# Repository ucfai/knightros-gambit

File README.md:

# Knightr0's Gambit

## Overview
This repository hosts the code for Knightr0's Gambit, a [University of Central Florida](https://www.ucf.edu) [AI](https://ucfai.org) / [IEEE](https://ieee.cecs.ucf.edu) collaboration to create an automatic chessboard (similar to [Harry Potter's Wizard Chess](https://www.youtube.com/watch?v=s3cjWc-XXCg) with less violence) powered by a custom chess AI.

<!--  -->

<!-- Video of chessboard in action: https://youtu.be/blah -->

[Project webpage](https://ucfai.github.io/knightros-gambit/), [project overview doc](https://docs.google.com/document/d/1CPY9yEVWDVO99mbckBnCJi-gKKobkBnB4XnjrLc4HFs/edit#)

<!-- Build guide: n/a -->

## How it works
<!--  -->
The main program is `game.py` (located in `firmware/raspi/`). This code is the entry point to interacting with the chessboard; it runs a loop that keeps track of game state (whose turn it is, past moves, etc.), computes moves using a custom chess AI, and processes images taken of the board to compute board state after the player moves a piece. This driver program has options for over-the-board play, a command-line interface, and a web interface. We plan to add a voice interface at a later point.

The `game.py` program runs on a Raspberry Pi, and interacts with arduino code that controls the actuators of the chessboard, the four interfaces (one-at-a-time) described above, a custom AI modeled after Deepmind's AlphaZero, and a computer vision system which keeps track of the current chessboard state.

The arduino code (located in `firmware/arduino/chessboard`) runs on an ESP32 microcontroller. 
Once the AI move has been computed on the Raspberry Pi, it is converted to a standardized message format and sent to the ESP32 microcontroller using UART serial communication. The microcontroller then actuates the physical board mechanism (motors and electromagnet) and sends back status messages indicating current state of the board/microcontroller. UART serial communication is used as it allows us to easily send data in both directions.

The AI is modeled after [Deepmind's AlphaZero](https://deepmind.com/blog/article/alphazero-shedding-new-light-grand-games-chess-shogi-and-go).
> To learn each game, an untrained neural network plays millions of games against itself via a process of trial and error called reinforcement learning. At first, it plays completely randomly, but over time the system learns from wins, losses, and draws to adjust the parameters of the neural network, making it more likely to choose advantageous moves in the future.

> The trained network is used to guide a search algorithm – known as Monte-Carlo Tree Search (MCTS) – to select the most promising moves in games. For each move, AlphaZero searches only a small fraction of the positions considered by traditional chess engines. In Chess, for example, it searches only 60 thousand positions per second in chess, compared to roughly 60 million for Stockfish.

<!-- A system diagram of the Arduino is shown below. -->
<!--  -->

<!-- ## How to Build Chessboard
Main documentation: blah.com

You can find the bill of materials, assembly instructions, software setup, etc at this website.
 -->

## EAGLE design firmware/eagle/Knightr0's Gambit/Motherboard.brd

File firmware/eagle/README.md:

# EAGLE Files
This directory will hold all of the files needed to open and view the EAGLE PCB design.

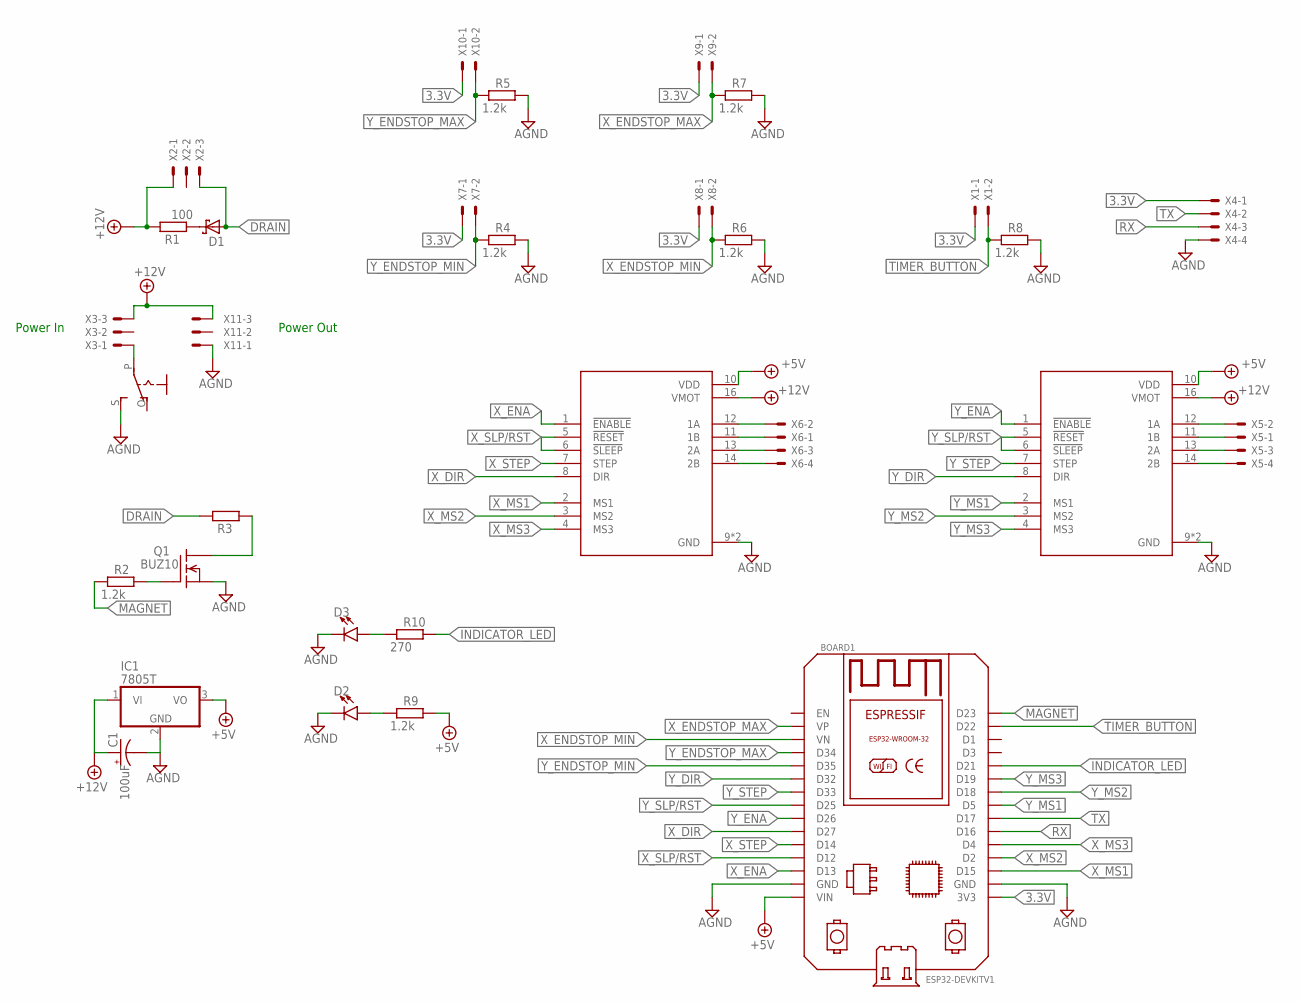
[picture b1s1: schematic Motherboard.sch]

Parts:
BOARD1: ESP32DEVKITV1; ESP32-DEVKITV1
C1: 100uF; B45181A
D1: SCHOTTKY-DIODEDO41; DO41-10
D2, D3: LED0603; LED-0603
IC1: 7805T; TO220H
Q1: BUZ10; TO220
R1: 100; R0603
R2, R4, R5, R6, R7, R8, R9: 1.2k; R0603
R3: R-EU_R0603; R0603
R10: 270; R0603
S1: EG1218S; EG1218
U1, U2: A4988_STEPPER_MOTOR_DRIVER_CARRIER; MODULE_A4988_STEPPER_MOTOR_DRIVER_CARRIER
X1, X7, X8, X9, X10: 22-23-2021
X2, X3, X11: 22-23-2031
X4, X5, X6: 22-23-2041

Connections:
3.3V: BOARD1.3V3, X1.1, X4.1, X7.1, X8.1, X9.1, X10.1
+5V: BOARD1.VIN, IC1.3 (VO), R9.2, U1.10 (VDD), U2.10 (VDD)
+12V: C1.+, IC1.1 (VI), R1.2, U1.16 (VMOT), U2.16 (VMOT), X2.1, X3.3, X11.3
AGND: BOARD1.GND, BOARD1.GND@1 (GND), C1.-, D2.C, D3.C, IC1.2 (GND), Q1.3 (S), R4.2, R5.2, R6.2, R7.2, R8.2, S1.S, U1.9 (GND), U1.15 (GND), U2.9 (GND), U2.15 (GND), X4.4, X11.1
DRAIN: D1.A, R3.2, X2.3
INDICATOR_LED: BOARD1.D21, R10.2
MAGNET: BOARD1.D23, R2.1
unnamed: U2.12 (1A), X5.2
unnamed: U2.11 (1B), X5.1
unnamed: U2.13 (2A), X5.3
unnamed: U2.14 (2B), X5.4
unnamed: U1.12 (1A), X6.2
unnamed: U1.11 (1B), X6.1
unnamed: D2.A, R9.1
unnamed: D3.A, R10.1
unnamed: Q1.2 (D), R3.1
unnamed: Q1.1 (G), R2.2
unnamed: D1.C, R1.1
unnamed: S1.P, X3.1
unnamed: U1.13 (2A), X6.3
unnamed: U1.14 (2B), X6.4
RX: BOARD1.D16, X4.3
TIMER_BUTTON: BOARD1.D22, R8.1, X1.2
TX: BOARD1.D17, X4.2
X_DIR: BOARD1.D27, U1.8 (DIR)
X_ENA: BOARD1.D13, U1.1 (!ENABLE)
X_ENDSTOP_MAX: BOARD1.VP, R7.1, X9.2
X_ENDSTOP_MIN: BOARD1.VN, R6.1, X8.2
X_MS1: BOARD1.D15, U1.2 (MS1)
X_MS2: BOARD1.D2, U1.3 (MS2)
X_MS3: BOARD1.D4, U1.4 (MS3)
X_SLP/RST: BOARD1.D12, U1.5 (!RESET), U1.6 (!SLEEP)
X_STEP: BOARD1.D14, U1.7 (STEP)
Y_DIR: BOARD1.D32, U2.8 (DIR)
Y_ENA: BOARD1.D26, U2.1 (!ENABLE)
Y_ENDSTOP_MAX: BOARD1.D34, R5.1, X10.2
Y_ENDSTOP_MIN: BOARD1.D35, R4.1, X7.2
Y_MS1: BOARD1.D5, U2.2 (MS1)
Y_MS2: BOARD1.D18, U2.3 (MS2)
Y_MS3: BOARD1.D19, U2.4 (MS3)
Y_SLP/RST: BOARD1.D25, U2.5 (!RESET), U2.6 (!SLEEP)
Y_STEP: BOARD1.D33, U2.7 (STEP)

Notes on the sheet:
Power In
Power Out

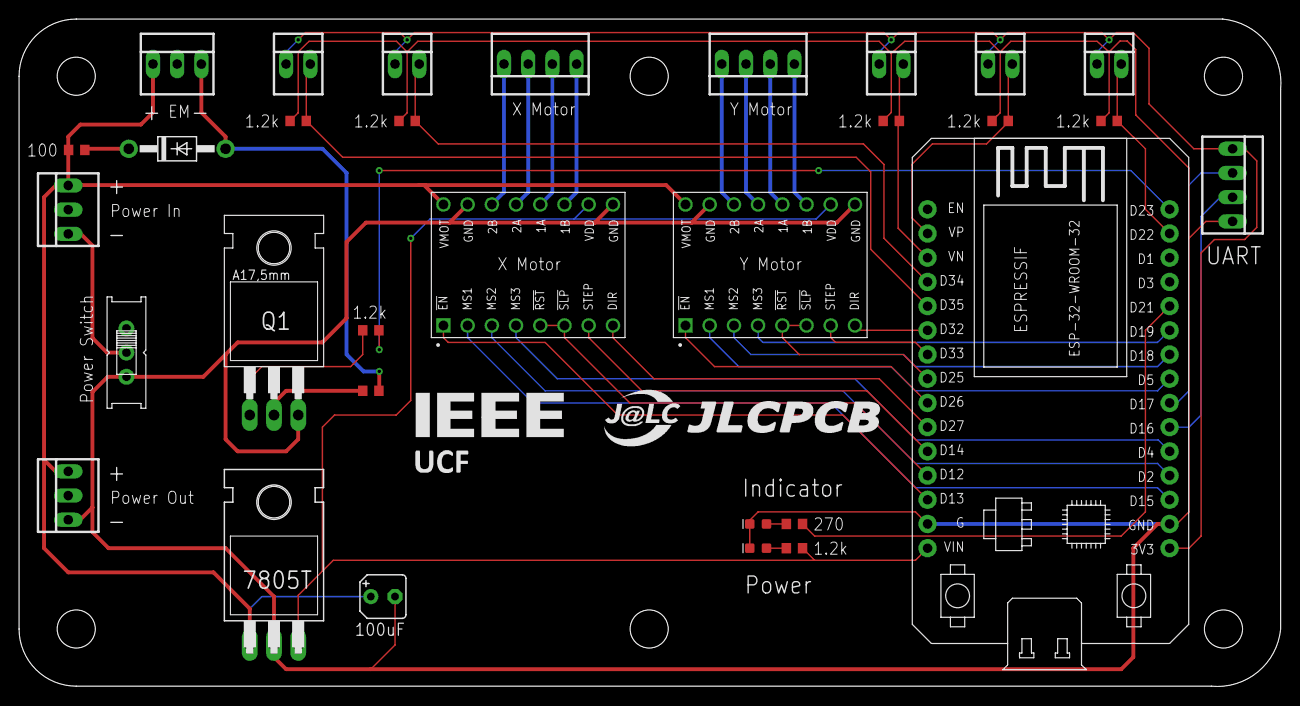
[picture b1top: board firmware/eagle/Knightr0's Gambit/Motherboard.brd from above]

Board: 2 copper layers, 132.4 x 70.0 mm, 31 parts (0 on the bottom side), 42 nets.

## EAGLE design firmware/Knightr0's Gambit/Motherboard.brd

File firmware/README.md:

# Firmware
This directory will hold code that controls actuation/sensing of the physical chessboard, as well as communication between the Arduino and the Raspberry Pi

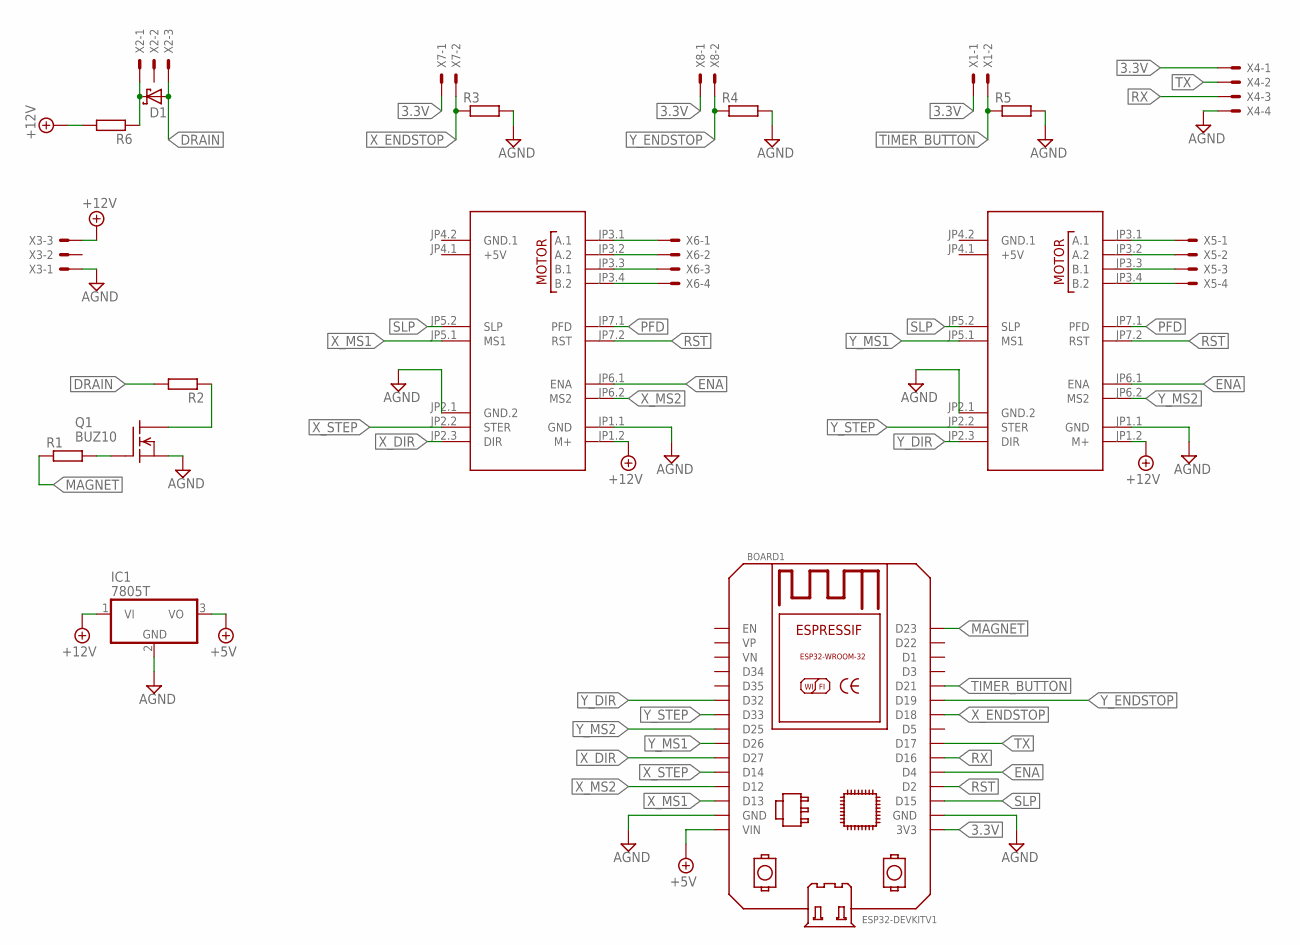
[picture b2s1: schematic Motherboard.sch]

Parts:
BOARD1: ESP32DEVKITV1; ESP32-DEVKITV1
D1: SCHOTTKY-DIODECB417-15; CB417-15
IC1: 7805T; TO220H
Q1: BUZ10; TO220
R1, R2, R3, R4, R5, R6: R-EU_R0603; R0603
U$1, U$2: STEPPER-MOTOR-EASY-DRIVER
X1, X7, X8: 22-23-2021
X2, X3: 22-23-2031
X4, X5, X6: 22-23-2041

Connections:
3.3V: BOARD1.3V3, X1.1, X4.1, X7.1, X8.1
+5V: BOARD1.VIN, IC1.3 (VO)
+12V: IC1.1 (VI), R6.2, U$1.JP1.2 (M+), U$2.JP1.2 (M+), X3.3
AGND: BOARD1.GND, BOARD1.GND@1 (GND), IC1.2 (GND), Q1.3 (S), R3.2, R4.2, R5.2, U$1.JP1.1 (GND), U$1.JP2.1 (GND.2), U$2.JP1.1 (GND), U$2.JP2.1 (GND.2), X3.1, X4.4
DRAIN: D1.A, R2.2, X2.3
ENA: BOARD1.D4, U$1.JP6.1 (ENA), U$2.JP6.1 (ENA)
MAGNET: BOARD1.D23, R1.1
unnamed: U$1.JP3.1 (A.1), X6.1
unnamed: U$1.JP3.2 (A.2), X6.2
unnamed: U$1.JP3.3 (B.1), X6.3
unnamed: U$1.JP3.4 (B.2), X6.4
unnamed: U$2.JP3.1 (A.1), X5.1
unnamed: U$2.JP3.2 (A.2), X5.2
unnamed: U$2.JP3.3 (B.1), X5.3
unnamed: U$2.JP3.4 (B.2), X5.4
unnamed: Q1.2 (D), R2.1
unnamed: Q1.1 (G), R1.2
unnamed: D1.C, R6.1, X2.1
PFD: U$1.JP7.1 (PFD), U$2.JP7.1 (PFD)
RST: BOARD1.D2, U$1.JP7.2 (RST), U$2.JP7.2 (RST)
RX: BOARD1.D16, X4.3
SLP: BOARD1.D15, U$1.JP5.2 (SLP), U$2.JP5.2 (SLP)
TIMER_BUTTON: BOARD1.D21, R5.1, X1.2
TX: BOARD1.D17, X4.2
X_DIR: BOARD1.D27, U$1.JP2.3 (DIR)
X_ENDSTOP: BOARD1.D18, R3.1, X7.2
X_MS1: BOARD1.D13, U$1.JP5.1 (MS1)
X_MS2: BOARD1.D12, U$1.JP6.2 (MS2)
X_STEP: BOARD1.D14, U$1.JP2.2 (STER)
Y_DIR: BOARD1.D32, U$2.JP2.3 (DIR)
Y_ENDSTOP: BOARD1.D19, R4.1, X8.2
Y_MS1: BOARD1.D26, U$2.JP5.1 (MS1)
Y_MS2: BOARD1.D25, U$2.JP6.2 (MS2)
Y_STEP: BOARD1.D33, U$2.JP2.2 (STER)

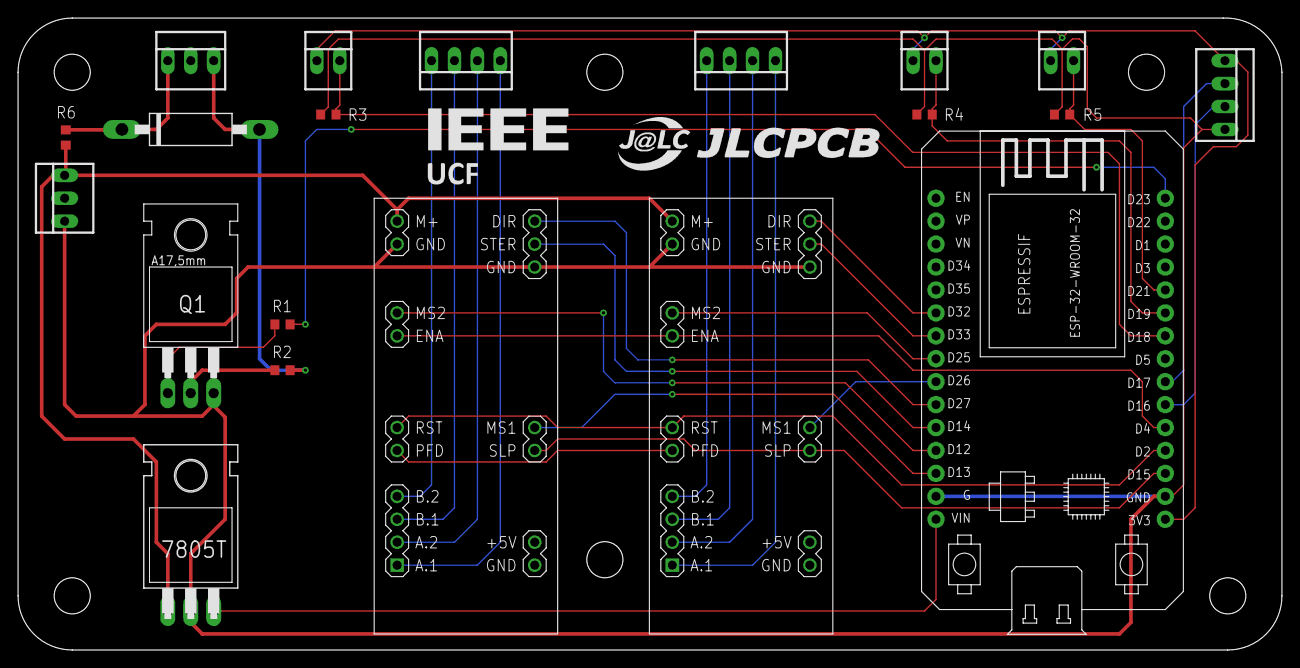
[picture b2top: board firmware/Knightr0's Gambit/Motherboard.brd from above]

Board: 2 copper layers, 140.0 x 70.0 mm, 20 parts (0 on the bottom side), 34 nets.

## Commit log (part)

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2022-02-13 changed homeAxis to allow for alignment of positive extremes as well
2022-02-13 Create stockfish wrapper to allow system agnostic creation of Stockfish object in stockfish_train
2022-02-13 Add ALIGN_AXIS and SET_ELECTROMAGNET opcodes
2022-02-13 Add clarifying comment to Message docstring
2022-02-13 Add function to request retransmitting last msg
2022-02-14 io file update
2022-02-15 Moved message processing and transmit function calls
2022-02-15 added spacing in alignAxis for readability
2022-02-15 fixed order of enum
2022-02-15 Removed .vscode folder and added .vscode directory name to .gitignore
2022-02-16 Add parser based on Lucas's prototype code
2022-02-16 modified motor direction preprocessors for clarification
2022-02-17 removed return in load_model
2022-02-17 Fixed device bug
2022-02-17 Resolved PR comments
2022-02-17 Created streamlit branch and added dashboard file
2022-02-17 Add README description explaining how to invoke train.py
2022-02-17 Fix import order in train
2022-02-17 Add dummy requirements.txt
2022-02-17 add newline
2022-02-19 Updated train.py to work with the dashboard and added additional features to the dashboard
2022-02-19 added comments for previous changes and fixed alignAxis current position computation placement
2022-02-22 Update argument handling to remove globals
2022-02-22 Remove test files from PR
2022-02-22 Print every 10th game
2022-02-24 Update streamlit dashboard
2022-02-24 Add debug messages to train.py
2022-02-24 Revert "Add arg parser to game"
2022-02-24 Fix outdated debug message in train.sh
    When arg is not streamlit or json, train.sh currently prints
    "Expected first argument to be either <streamlit> or <cli>" which is incorrect.
2022-02-24 Fixed 0/0 bug
2022-02-24 typo : )
2022-02-24 Made training flags, split stock dataset creation Also made it so it doesnt crash if the dataset directory doesnt exist
2022-02-25 Added new end stop switches
2022-02-25 Changed the name of errorFlag to uartMessageIncompleteFlag for clarity
2022-02-26 Changed to new pinout for endstops
2022-02-27 added necessary PWM setup for future ledcWrite use
2022-02-27 fixed further style mistakes
2022-03-01 Move arg parsing to util
2022-03-01 Calling .reverse() on chess_grid lead to bug with piece captures. Fixed
2022-03-01 Add parsing of pgn file to list of uci_moves
2022-03-01 Fix docstring
2022-03-01 Update parse_test_file
2022-03-01 Update comments in parse_test_file
2022-03-01 Move game loop into class based approach with process method
2022-03-01 Add methods to expose info needed for GUI
2022-03-01 Fix scholar's mate
2022-03-01 Added definitions for OpCode and ArduinoStatus message lengths
2022-03-02 Update test1.txt to have same commands as test1.pgn, but expressed as Message types
2022-03-02 Add test file with Instruction type messages
2022-03-02 Add function for transposing a board cell
2022-03-02 Fix pylint errors
2022-03-03 updated member page
2022-03-08 corrected error handling function format and removed incorrect function calls
2022-03-09 corrected comment
2022-03-12 update eagle files
2022-03-13 Update align axis to allow more granularity. Can now specify to align with xmin, xmax, ymin, or ymax.
2022-03-13 Remove text from buttons
2022-03-13 Remove dead lines
2022-03-15 implemented main structure of movement functions
2022-03-15 updated point calculations and accounted for potential edge cases
2022-03-16 Changed order of values in message array for sendMessageToPi()
2022-03-16 Fixed indexing for Instruction messages
2022-03-17 added msd and updated links
2022-03-18 Added comment to explain sentMessage[]
2022-03-19 removed old implementation of movement primitive calls
2022-03-19 added remaining cases for moveAlongEdges
2022-03-19 added movement function result handling and updated format
2022-03-22 Added comments
2022-03-22 Updated return value
2022-03-23 Updated recursive call, naming, and comments
2022-03-23 Updated recursive call and added comments explaining it
2022-03-23 Added edge case where moveDirect is used to path to starting point with an invalid slope
2022-03-24 Simplified repeated code using a pointer for the motor
2022-03-24 Updated statusCodeHandler behavior and related calls
2022-03-24 Simplified code with updated handler logic, fixed incorrect return
2022-03-24 Updated residual layers
2022-03-25 Updated moveDirect so electromagnet accounts for moving to the start position
2022-03-25 Added comment
2022-03-25 Fixed path issue
2022-03-26 Fix order of return statement
2022-03-26 Update shebang line in bash script so that it works for zsh shell
2022-03-26 Add TrainingFlags class to simplify return statements and fixed pylint errors
2022-03-26 Fix variable naming
2022-03-29 Add structure for page frames and fix coloring of cells
2022-03-29 Update Instruction message handling scheme and add calls to alignaxis
2022-03-29 Update InstructionType enum, fixed message validation
2022-03-30 Make directory for opcodegenerator
2022-03-30 implement frames for each page, added page for centering piece
2022-03-30 Fix some pylint warnings
2022-03-31 started alignAxis adjustment for further review
2022-03-31 Corrected code in accordance to functionality and added comments
2022-03-31 Fixed valid range for ALIGN_AXIS extra byte
2022-03-31 Testing API Key as environment variable
2022-03-31 comment change
2022-03-31 Getting figshare api set up
2022-04-01 Added debug flag
2022-04-01 Added debug messages to main functions
2022-04-01 Updated debug print statements and comments
2022-04-01 Updated tab width to 2 spaces
2022-04-01 Updated spacing for while loops
2022-04-01 Updated spacing surrounding && and || comparisons to one space
2022-04-01 Updated name and comments
2022-04-02 Updated equal and not equal comparisons
2022-04-02 Wrapped repeated code into a function
2022-04-02 Updated for loops to remove variable declaration inside the loop argument fields
2022-04-02 Updated spacing
2022-04-02 Add code for calling home() on Arduino directly. Also changed OpType to InstructionType
2022-04-02 Updated preprocessors to enums for better organization
2022-04-02 Updated enum index name
2022-04-03 Update message sending to send bytes
2022-04-03 Implement receiving messages from Arduino, safeguard all comms with --microcontroller flag
2022-04-03 Update if statement to use is None comparison
2022-04-03 Fix serial import order and function call to check if buffer is nonempty
2022-04-03 Updated variable and function argument datatypes to reduce wasted memory
2022-04-03 Fixed compilation errors
2022-04-03 Getting the figshare API to work with current ways of saving dataset and models
2022-04-03 Updated variable names to be consistent with similar variables in movementFunction.ino
2022-04-04 Remove out-of-date TODOs and make other small fixes
2022-04-04 Update all docstrings to use triple quotes
2022-04-04 Add disable import error for 3P libraries
2022-04-04 Removed unnecessary newline spaces
2022-04-04 Removed curly braces from if statement with single line of code
2022-04-04 Fixed alignAxis bug and formatting
2022-04-04 Removed eighthStepsPerPulse since it was not used, also updated formatting accordingly
2022-04-04 Short term fix to replace SerialEvent2()
2022-04-05 Added buffer clear on duplicates
2022-04-05 Initial model evaluation code
2022-04-05 Updated debug print statements to use debug levels instead
2022-04-05 Removed testing.py
2022-04-06 Update prompt when running in debug mode
2022-04-07 Added semi-colon to fix compile error
2022-04-07 Changed model_path to null
2022-04-07 Update align axis description and add '4' as valid extra.
2022-04-07 Update opcodegenerator to have colors that may show on windows ??
2022-04-08 Make buttons not resize
2022-04-08 Remove last instance of DEFAULT_FONT
2022-04-08 Fix decoding of serial message from Arduino
2022-04-09 Add files via upload
    For the promotable chess piece code (http://www.raspberryturk.com/notebooks/chess_piece_classification.html) what did we need to change with it?
2022-04-10 Fix comparison to int move count failing when checking serial msg
2022-04-10 added error handling cases in test overview
2022-04-11 Removed error message transmission
2022-04-11 added single comment for promotion in test overview
2022-04-12 Fixed 2 bugs (sry for bad commit msg)
2022-04-13 Some more changes to ai_io
2022-04-13 Add error types for Arduino
2022-04-13 Add instruction for setting human move valid flag to GUI
2022-04-13 Fixed parameter issue
2022-04-13 Removed figshare upload
2022-04-13 Fixed pylint spacing
2022-04-13 Disable chess timer button after press
2022-04-14 Added stockfish heuristic mixing
2022-04-16 Add files via upload
    I am having trouble with the NumPy load function and I cannot seem to understand why (https://numpy.org/doc/stable/reference/generated/numpy.load.html), so a code review would be appreciated. Note th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
2022-04-17 Updated motor driver pins to be separate, added initial disableMotor call
2022-04-18 Updated pins for more consistent wiring
2022-04-19 Finalizing figshare
2022-04-19 Fix pylint warnings for stockfish_train
2022-04-19 Fix pylint warnings for train
2022-04-19 Fix pylint warnings for figshare_api
2022-04-19 Fix pylint warnings for state_representation
2022-04-19 Fix pylint warnings for nn_layout
2022-04-19 Remove unneeded space from comment
2022-04-19 Fix spacing and typos in file
2022-04-20 removing info frame
2022-04-20 adding docstrings to gui.py
2022-04-21 Resolving pull request
2022-04-21 formatting changes
2022-04-21 Made classes for model saving and dataset saving
2022-04-22 Update some style things
2022-04-22 changing loop structure
2022-04-22 Update script to use python 3
2022-04-22 Fix quote format
2022-04-22 Reduced length of time.sleep and made printing board status optional with use of the verbose flag
2022-04-27 adjusting for human player to play as black and fixed highlighting for invalid moves
2022-04-29 Edit existing and add more debug print statements
2022-04-29 Edit print statements, group sleep and reset pins
2022-04-29 Added MS3 pin and included support for 16th steps
2022-04-29 Updated motor pins to simplify schematic
2022-04-29 Updated pin definition to simplify circuit
2022-05-01 Compacted electromagnet print statements and initialized currPositions in setup
2022-05-01 Updated print statements
2022-05-03 Updated pcb files
2022-05-18 Updated bug
2022-05-27 added indicator to EM
2022-05-30 fixing pr comments and styling code
2022-06-04 Added enable/disable motor uart commands
2022-06-05 Add RESET_ARDUINO to VALID_INSTRUCTIONS
2022-06-05 Rename reset_arduino to restart_arduino
2022-07-30 Added h1 tag
2022-07-30 Delete processed
    Should be a folder not file
2022-08-22 Remove unused board.fen file
2022-09-05 Updated README for chess-AI
2022-09-06 Add stockfish path for Windows OS
2022-09-06 Fix order of requirements and update to latest version.
2022-09-07 Added castling feature
2022-09-07 fixing random turn at start
2022-09-08 Stockfish model checkpointing
2022-09-08 Update model_evaluation.py
    replaces repetitive code with function make_move(). There is a bit more I could replace with a function but I found it looked gross bc I had to replace the break statements with a boolean variable an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
2022-09-09 Added way to pass in model path for evaluation
2022-09-25 Added print statements to train.py
2022-10-08 Fixed enum
2022-10-27 Update train.py
    fixed trained inefficiency that made training on different batch sizes way less impactful. Also added distributed data parallel capabilities, just need to change how the mcts is trained in parallel.
2022-10-27 Update nn_layout.py
    remove old device settings since they shouldn't be needed with the new parallelization implementation.
2023-01-15 Changed disable command from digitalWrite to ledcWrite
2023-01-29 Changed EM disable and wrote alignPiece()
2023-02-12 Add enableMotors()
2023-02-13 corner detection update
    Gets basic layout for corner detection, still needs some fixing up. Main problem is it also detects the corner of the image itself. Changed threshold function to adaptiveThreshold to improve how it d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

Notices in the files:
parts and their libraries:
Ultrasonic Sensor: Released under the Creative Commons Attribution 4.0 International License: http://creativecommons.org/licenses/by/4.0
SparkFun-LED: Licensing: Creative Commons ShareAlike 4.0 International - https://creativecommons.org/licenses/by-sa/4.0
